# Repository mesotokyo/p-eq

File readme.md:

# MST P-EQ (Program Equalizer) schematic and PCB for KiCAD

(Japanese version is [here](readme_ja.md) / 日本語版は[こちら](readme_ja.md))

## What is this?

KiCAD files to build PCB of the MST P-EQ (Program Equalizer). These files are created with KiCad 6.0.

For more information about MST P-EQ, please check https://meso.tokyo/works/p-eq .

## Notice

This schematic and PCB file need a `ak_misc` footprint library in [mst-kicad-lib](https://github.com/mesotokyo/mst-kicad-lib). 

## DISCLAIMER

FILES IN THIS REPOSITORY ARE PROVIDED "AS IS", WITHOUT WARRANTY OF ANY KIND, EXPRESS OR IMPLIED, INCLUDING BUT NOT LIMITED TO THE WARRANTIES OF MERCHANTABILITY, FITNESS FOR A PARTICULAR PURPOSE AND NONINFRINGEMENT. IN NO EVENT SHALL THE AUTHORS OR COPYRIGHT HOLDERS BE LIABLE FOR ANY CLAIM, DAMAGES OR OTHER LIABILITY, WHETHER IN AN ACTION OF CONTRACT, TORT OR OTHERWISE, ARISING FROM, OUT OF OR IN CONNECTION WITH IN FILES IN THIS REPOSITORY OR THE USE OR OTHER DEALINGS IN FILES IN THIS REPOSITORY.

## License

CC BY 4.0. For more information, please check https://creativecommons.org/licenses/by/4.0/ .

## Author

MST/mesotokyo

 - https://meso.tokyo/
 - https://x.com/mesotokyox

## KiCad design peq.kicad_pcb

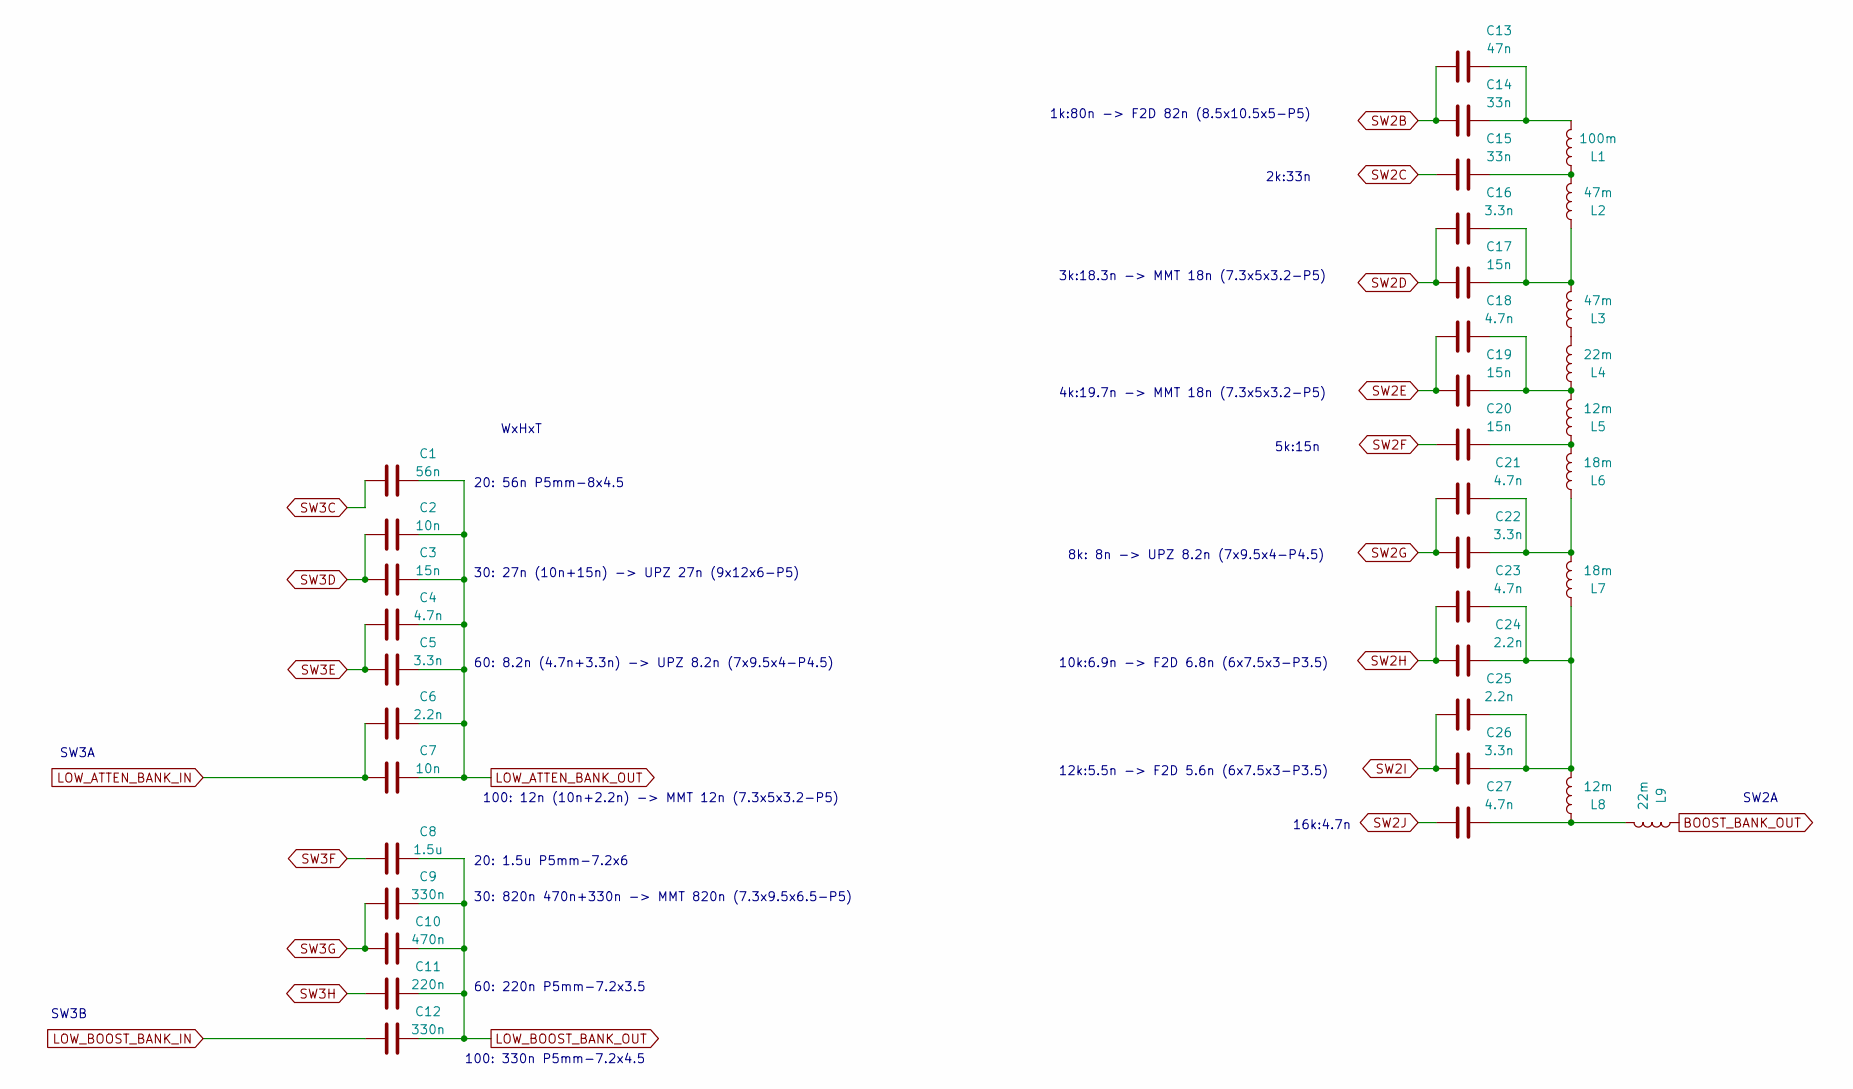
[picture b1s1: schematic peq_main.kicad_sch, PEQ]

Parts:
C1: 56n; C_Rect_L7.2mm_W4.5mm_P5.00mm_FKS2_FKP2_MKS2_MKP2
C2, C7: 10n; C_Rect_L7.2mm_W2.5mm_P5.00mm_FKS2_FKP2_MKS2_MKP2
C3, C17, C19, C20: 15n; C_Rect_L7.2mm_W2.5mm_P5.00mm_FKS2_FKP2_MKS2_MKP2
C4, C18, C21, C23, C27: 4.7n; C_Rect_L7.2mm_W2.5mm_P5.00mm_FKS2_FKP2_MKS2_MKP2
C5, C16, C22, C26: 3.3n; C_Rect_L7.2mm_W2.5mm_P5.00mm_FKS2_FKP2_MKS2_MKP2
C6, C24, C25: 2.2n; C_Rect_L7.2mm_W2.5mm_P5.00mm_FKS2_FKP2_MKS2_MKP2
C8: 1.5u; C_Rect_L7.2mm_W7.2mm_P5.00mm_FKS2_FKP2_MKS2_MKP2
C9, C12: 330n; C_Rect_L7.2mm_W4.5mm_P5.00mm_FKS2_FKP2_MKS2_MKP2
C10: 470n; C_Rect_L7.2mm_W5.5mm_P5.00mm_FKS2_FKP2_MKS2_MKP2
C11: 220n; C_Rect_L7.2mm_W3.5mm_P5.00mm_FKS2_FKP2_MKS2_MKP2
C13: 47n; C_Rect_L7.2mm_W2.5mm_P5.00mm_FKS2_FKP2_MKS2_MKP2
C14, C15: 33n; C_Rect_L7.2mm_W2.5mm_P5.00mm_FKS2_FKP2_MKS2_MKP2
L1: 100m; L_Radial_D10.5mm_P5.00mm_Abacron_AISR-01
L2, L3: 47m; L_Axial_L7.0mm_D3.3mm_P10.16mm_Horizontal_Fastron_MICC
L4, L9: 22m; L_Axial_L7.0mm_D3.3mm_P10.16mm_Horizontal_Fastron_MICC
L5, L8: 12m; L_Axial_L7.0mm_D3.3mm_P10.16mm_Horizontal_Fastron_MICC
L6, L7: 18m; L_Axial_L7.0mm_D3.3mm_P10.16mm_Horizontal_Fastron_MICC

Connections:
BOOST_BANK_OUT: L9.1; also elsewhere on the board
EQ_OUT: C1.2, C2.2, C3.2, C4.2, C5.2, C6.2, C7.2; also elsewhere on the board
LOW_ATTEN_BANK_IN: C6.1, C7.1; also elsewhere on the board
LOW_BOOST_BANK_IN: C12.1; also elsewhere on the board
LOW_BOOST_BANK_OUT: C8.2, C9.2, C10.2, C11.2, C12.2; also elsewhere on the board
unnamed: C13.2, C14.2, L1.2
unnamed: C15.2, L1.1, L2.2
unnamed: C16.2, C17.2, L2.1, L3.2
unnamed: C18.2, C19.2, L4.1, L5.2
unnamed: C20.2, L5.1, L6.2
unnamed: C21.2, C22.2, L6.1, L7.2
unnamed: C23.2, C24.2, C25.2, C26.2, L7.1, L8.2
unnamed: C27.2, L8.1, L9.2
unnamed: L3.1, L4.2
SW2B: C13.1, C14.1; also elsewhere on the board
SW2C: C15.1; also elsewhere on the board
SW2D: C16.1, C17.1; also elsewhere on the board
SW2E: C18.1, C19.1; also elsewhere on the board
SW2F: C20.1; also elsewhere on the board
SW2G: C21.1, C22.1; also elsewhere on the board
SW2H: C23.1, C24.1; also elsewhere on the board
SW2I: C25.1, C26.1; also elsewhere on the board
SW2J: C27.1; also elsewhere on the board
SW3C: C1.1; also elsewhere on the board
SW3D: C2.1, C3.1; also elsewhere on the board
SW3E: C4.1, C5.1; also elsewhere on the board
SW3F: C8.1; also elsewhere on the board
SW3G: C9.1, C10.1; also elsewhere on the board
SW3H: C11.1; also elsewhere on the board

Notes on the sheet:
30: 820n 470n+330n -> MMT 820n (7.3x9.5x6.5-P5)
SW2A
SW3A
60: 220n P5mm-7.2x3.5
SW3B
5k:15n
100: 12n (10n+2.2n) -> MMT 12n (7.3x5x3.2-P5)
10k:6.9n -> F2D 6.8n (6x7.5x3-P3.5)
100: 330n P5mm-7.2x4.5
4k:19.7n -> MMT 18n (7.3x5x3.2-P5)
WxHxT
60: 8.2n (4.7n+3.3n) -> UPZ 8.2n (7x9.5x4-P4.5)
2k:33n
20: 1.5u P5mm-7.2x6
8k: 8n -> UPZ 8.2n (7x9.5x4-P4.5)
1k:80n -> F2D 82n (8.5x10.5x5-P5)
20: 56n P5mm-8x4.5
30: 27n (10n+15n) -> UPZ 27n (9x12x6-P5)
16k:4.7n
3k:18.3n -> MMT 18n (7.3x5x3.2-P5)
12k:5.5n -> F2D 5.6n (6x7.5x3-P3.5)

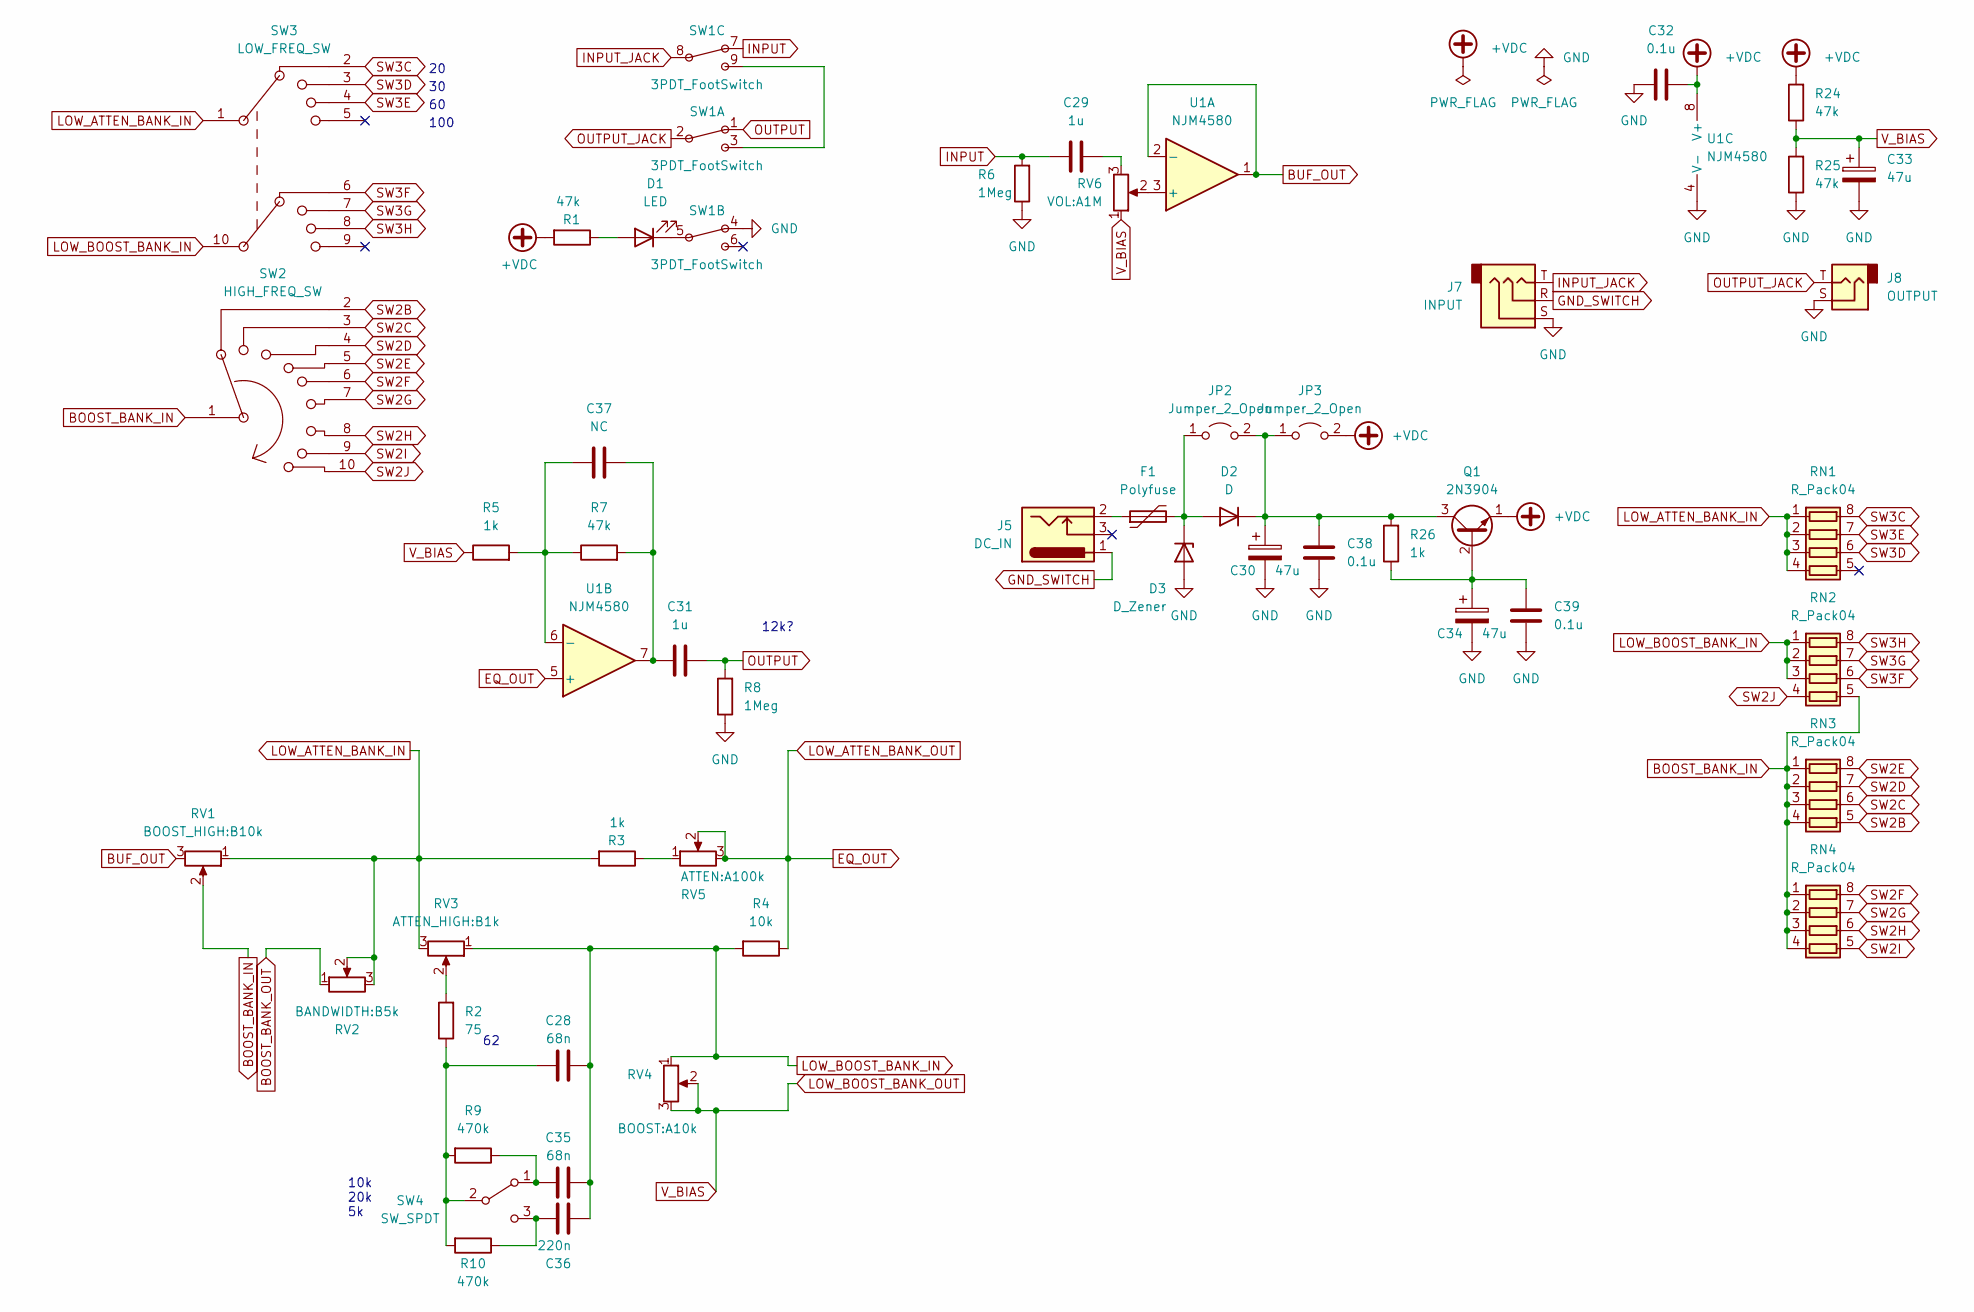
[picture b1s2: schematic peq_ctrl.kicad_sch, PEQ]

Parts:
C28, C35: 68n; C_Rect_L7.2mm_W4.5mm_P5.00mm_FKS2_FKP2_MKS2_MKP2
C29, C31: 1u; C_Rect_L7.2mm_W7.2mm_P5.00mm_with_SMD_3216
C30, C33, C34: 47u; CP_Radial_D6.3mm_P2.50mm
C32: 0.1u; C_Disc_D5.0mm_W2.5mm_P2.50mm
C36: 220n; C_Rect_L7.2mm_W3.5mm_P5.00mm_FKS2_FKP2_MKS2_MKP2
C37: NC; C_0805_2012Metric_Pad1.18x1.45mm_HandSolder
C38, C39: 0.1u; C_0805_2012Metric_Pad1.18x1.45mm_HandSolder
D1: LED; LED_D3.0mm
D2: D; D_DO-35_SOD27_P7.62mm_Horizontal
D3: D_Zener; D_DO-35_SOD27_P2.54mm_Vertical_AnodeUp
F1: Polyfuse; R_Axial_DIN0204_L3.6mm_D1.6mm_P5.08mm_Horizontal
J5: DC_IN; JST_XH_B3B-XH-A_1x03_P2.50mm_Vertical
J7: INPUT; Jack_Pad_TRS
J8: OUTPUT; Jack_Pad_TS
JP2, JP3: Jumper_2_Open; SolderJumper-2_P1.3mm_Open_RoundedPad1.0x1.5mm
Q1: 2N3904; TO-92
R1, R7, R24, R25: 47k; R_Axial_DIN0207_L6.3mm_D2.5mm_P7.62mm_with_SMD
R2: 75; R_Axial_DIN0207_L6.3mm_D2.5mm_P7.62mm_with_SMD
R3, R5, R26: 1k; R_Axial_DIN0207_L6.3mm_D2.5mm_P7.62mm_with_SMD
R4: 10k; R_Axial_DIN0207_L6.3mm_D2.5mm_P7.62mm_with_SMD
R6, R8: 1Meg; R_Axial_DIN0207_L6.3mm_D2.5mm_P7.62mm_with_SMD
R9, R10: 470k; R_0805_2012Metric_Pad1.20x1.40mm_HandSolder
RN1, RN2, RN3, RN4: R_Pack04; R_Array_Convex_4x0603_handsolder
RV1: BOOST_HIGH:B10k; POT-16mm
RV2: BANDWIDTH:B5k; POT-16mm
RV3: ATTEN_HIGH:B1k; POT-16mm
RV4: BOOST:A10k; POT-16mm
RV5: ATTEN:A100k; POT-16mm
RV6: VOL:A1M; POT-16mm
SW1: 3PDT_FootSwitch; 3PDT_FootSwitch_ovalpad
SW2: HIGH_FREQ_SW; SR1712F-XXXX-15K0A-B9-N-027-oval
SW3: LOW_FREQ_SW; SR1712F-XXXX-15K0A-B9-N-027-oval
SW4: SW_SPDT; spdt-sw-micro-with-fixer
U1: NJM4580; DIP-8_W7.62mm_Socket_w_SOP8

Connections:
+VDC: C32.2, JP3.2 (B), Q1.1 (E), R1.2, R24.2, U1.8 (V+)
BOOST_BANK_IN: RN2.5 (R4.2), RN3.1 (R1.1), RN3.2 (R2.1), RN3.3 (R3.1), RN3.4 (R4.1), RN4.1 (R1.1), RN4.2 (R2.1), RN4.3 (R3.1), RN4.4 (R4.1), RV1.2, SW2.1
BOOST_BANK_OUT: RV2.1; also elsewhere on the board
BUF_OUT: RV1.3, U1.1, U1.2 (-)
EQ_OUT: R4.1, RV5.2, RV5.3, U1.5 (+); also elsewhere on the board
GND: C30.2, C32.1, C33.2, C34.2, C38.1, C39.1, D3.2 (A), J7.S, J8.S, R6.1, R8.1, R25.1, SW1.4, U1.4 (V-)
GND_SWITCH: J5.1, J7.R
INPUT: C29.1, R6.2, SW1.7
INPUT_JACK: J7.T, SW1.8
LOW_ATTEN_BANK_IN: R3.2, RN1.1 (R1.1), RN1.2 (R2.1), RN1.3 (R3.1), RN1.4 (R4.1), RV1.1, RV2.2, RV2.3, RV3.3, SW3.1; also elsewhere on the board
LOW_BOOST_BANK_IN: C28.2, C35.2, C36.2, R4.2, RN2.1 (R1.1), RN2.2 (R2.1), RN2.3 (R3.1), RV3.1, RV4.1, SW3.10; also elsewhere on the board
LOW_BOOST_BANK_OUT: C33.1, R5.1, R24.1, R25.2, RV4.2, RV4.3, RV6.1; also elsewhere on the board
unnamed: C28.1, R2.1, R9.2, R10.2, SW4.2 (B)
unnamed: C29.2, RV6.3
unnamed: C31.1, C37.2, R7.2, U1.7
unnamed: C34.1, C39.2, Q1.2 (B), R26.1
unnamed: C35.1, R9.1, SW4.1 (A)
unnamed: C36.1, R10.1, SW4.3 (C)
unnamed: C37.1, R5.2, R7.1, U1.6 (-)
unnamed: D1.1 (K), SW1.5
unnamed: D1.2 (A), R1.1
unnamed: D2.2 (A), D3.1 (K), F1.2, JP2.1 (A)
unnamed: F1.1, J5.2
unnamed: C30.1, C38.2, D2.1 (K), JP2.2 (B), JP3.1 (A), Q1.3 (C), R26.2
unnamed: R2.2, RV3.2
unnamed: R3.1, RV5.1
unnamed: RV6.2, U1.3 (+)
unnamed: SW1.3, SW1.9
OUTPUT: C31.2, R8.2, SW1.1
OUTPUT_JACK: J8.T, SW1.2
SW2B: RN3.5 (R4.2), SW2.2; also elsewhere on the board
SW2C: RN3.6 (R3.2), SW2.3; also elsewhere on the board
SW2D: RN3.7 (R2.2), SW2.4; also elsewhere on the board
SW2E: RN3.8 (R1.2), SW2.5; also elsewhere on the board
SW2F: RN4.8 (R1.2), SW2.6; also elsewhere on the board
SW2G: RN4.7 (R2.2), SW2.7; also elsewhere on the board
SW2H: RN4.6 (R3.2), SW2.8; also elsewhere on the board
SW2I: RN4.5 (R4.2), SW2.9; also elsewhere on the board
SW2J: RN2.4 (R4.1), SW2.10; also elsewhere on the board
SW3C: RN1.8 (R1.2), SW3.2; also elsewhere on the board
SW3D: RN1.6 (R3.2), SW3.3; also elsewhere on the board
SW3E: RN1.7 (R2.2), SW3.4; also elsewhere on the board
SW3F: RN2.6 (R3.2), SW3.6; also elsewhere on the board
SW3G: RN2.7 (R2.2), SW3.7; also elsewhere on the board
SW3H: RN2.8 (R1.2), SW3.8; also elsewhere on the board

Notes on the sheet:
12k?
100
10k 20k 5k

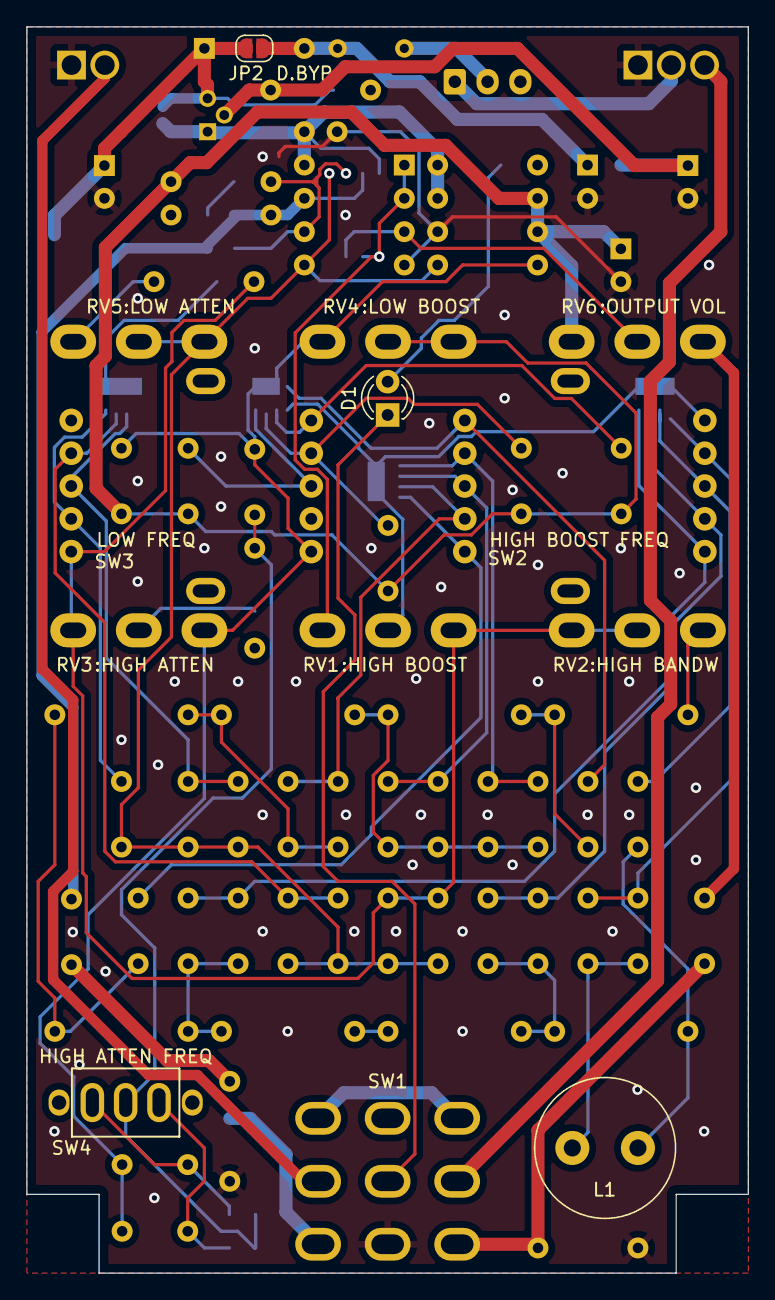
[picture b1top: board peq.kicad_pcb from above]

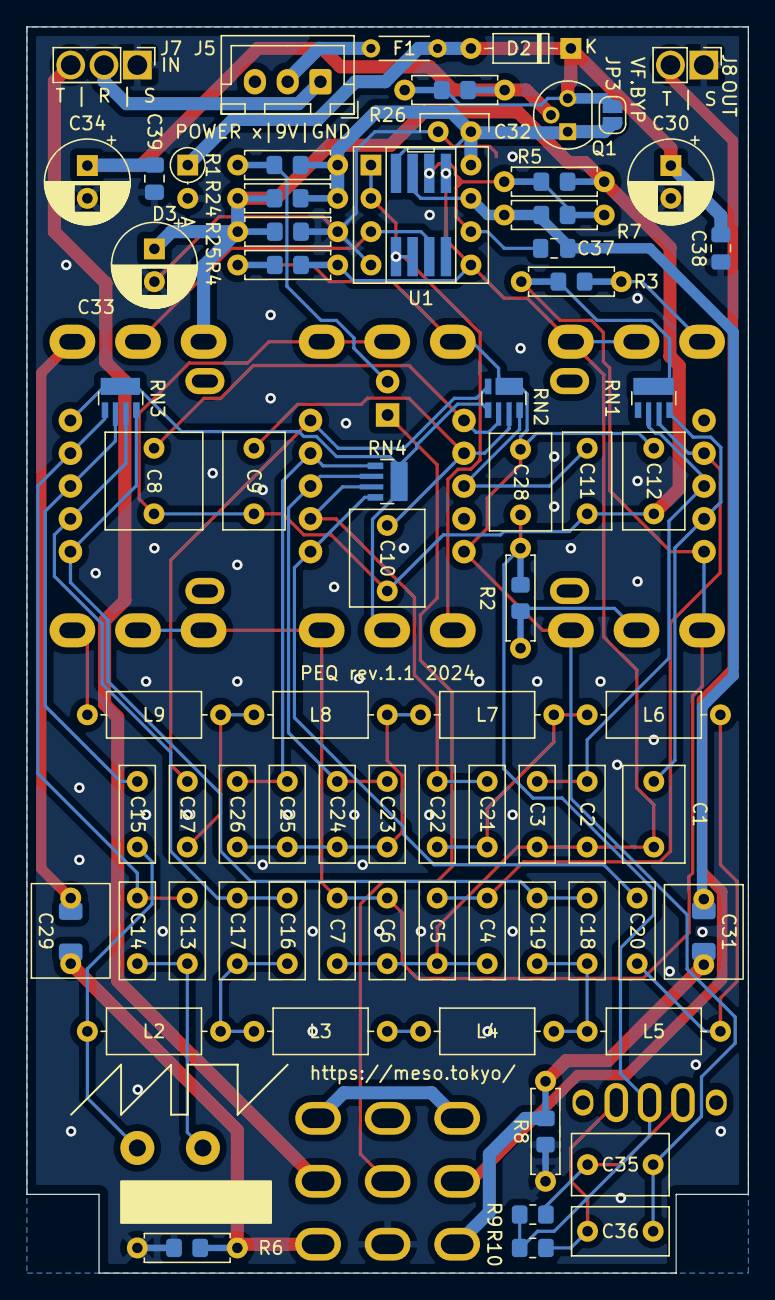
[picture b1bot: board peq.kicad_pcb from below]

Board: 2 copper layers, 55.0 x 95.0 mm, 86 parts (73 on the bottom side), 54 nets.

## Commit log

2024-09-26 update and clean up Fab layer
2024-09-26 change values: R7 to 47k, RV2 to B5k
2024-09-28 add protection components and fix layout
2024-11-02 update comments and credits
